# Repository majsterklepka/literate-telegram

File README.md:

# literate-telegram
moduł zasilacza stabilizowanego

Dwa moduły zasilacza stabilizowanego, przygotowane do wykonania jako DIY:

Moduły wykorzystują popularne liniowe stabilizatory napięcia stałego z rodziny 78xx i 79xx , kilka elementów dyskretnych, posiada bocznik prądowy.

Przygotowany został również projekt płytki drukowanej, oraz rysunek płytki w formacie PNG, 100x100mm, 2x2 moduły do wykonania w  domu. Rysunek płytki zawiera po 2 takie same moduły:

## Credits

Oczywiście jak i pozostałe moje projekty i ten jest udostępniany na zasadach Wolnych Licencji:

- [CC-BY-SA 4.0](https://creativecommons.org/licenses/by-sa/4.0/ "License")

Co mogę dodać? => Baw się dobrze, podziel się tym projektem z przyjaciółmi i niezapominaj o Autorze(ach);)

_MSc. Paweł Sobótka (SQ7EQE)_

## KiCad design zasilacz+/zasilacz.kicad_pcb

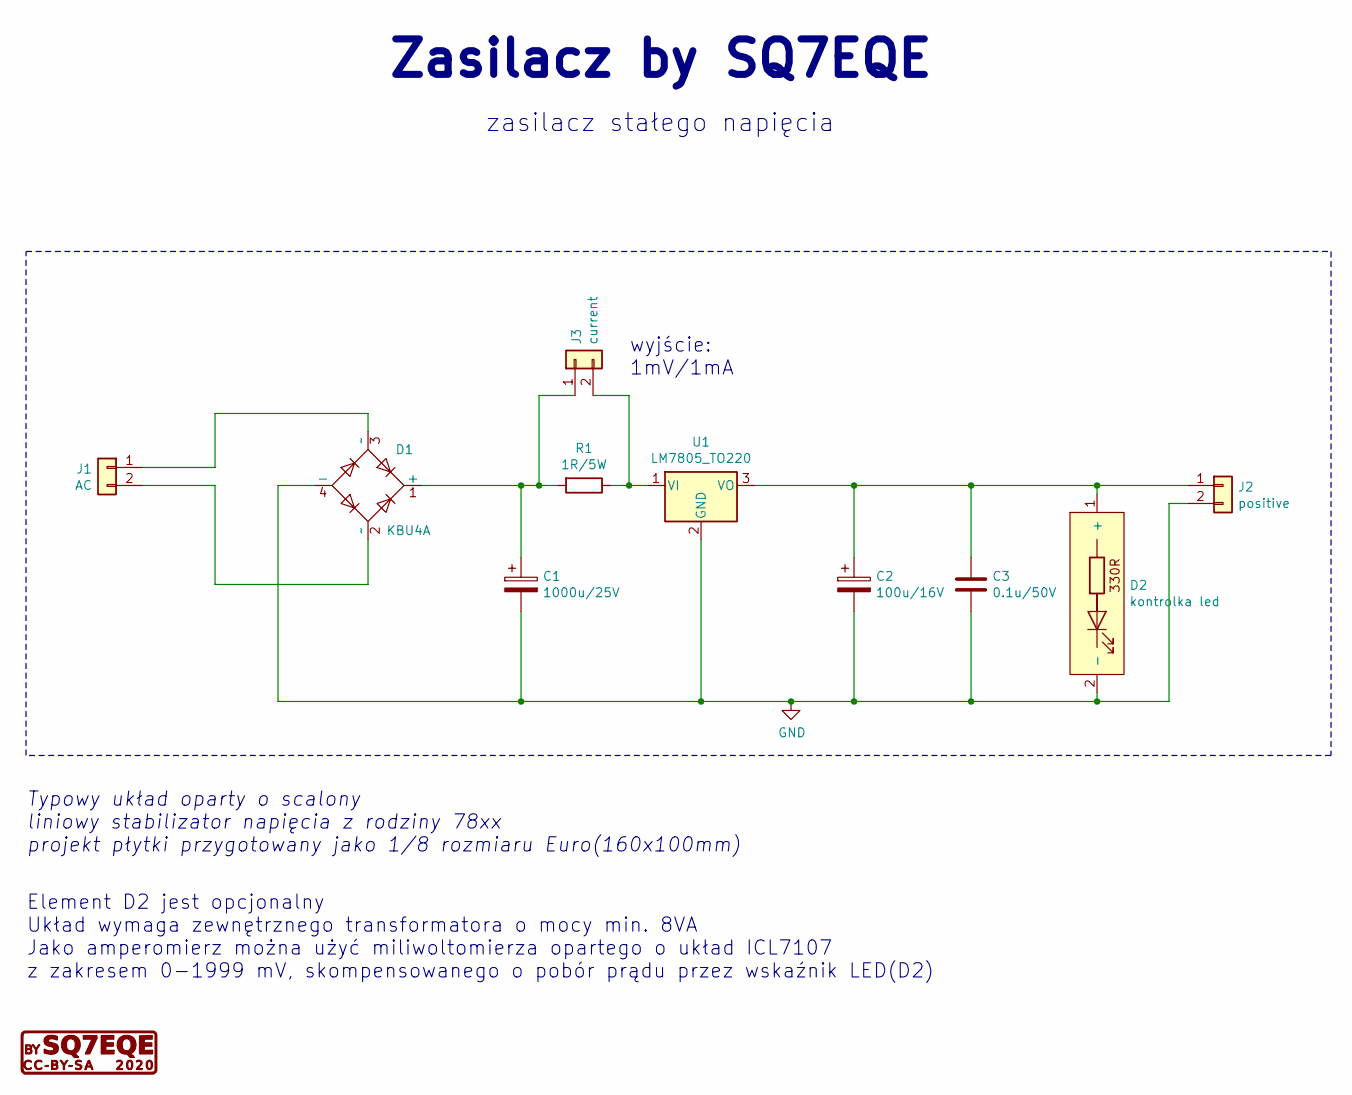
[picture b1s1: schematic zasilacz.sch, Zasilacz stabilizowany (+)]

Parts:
C1: 1000u/25V; CP_Radial_D10.0mm_P5.00mm
C2: 100u/16V; CP_Radial_D7.5mm_P2.50mm
C3: 0.1u/50V; C_Rect_L4.6mm_W5.5mm_P2.50mm_MKS02_FKP02
D1: KBU4A; Diode_Bridge_Vishay_KBU
D2: kontrolka led; led-indicators
J1: AC; conn-01x02_5.08mm
J2: positive; conn-01x02_5.08mm
J3: current; conn-01x02_5.08mm
R1: 1R/5W; R_Axial_Power_L25.0mm_W9.0mm_P27.94mm
U1: LM7805_TO220; TO-220-3_Vertical

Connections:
GND: C1.2, C2.2, C3.2, D1.4 (-), D2.2 (-), J2.2, U1.2 (GND)
unnamed: C1.1, D1.1 (+), J3.1, R1.2
unnamed: C2.1, C3.1, D2.1 (+), J2.1, U1.3 (VO)
unnamed: D1.2 (~~), J1.2
unnamed: D1.3 (~~), J1.1
unnamed: J3.2, R1.1, U1.1 (VI)

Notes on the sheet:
Typowy układ oparty o scalony liniowy stabilizator napięcia z rodziny 78xx projekt płytki przygotowany jako 1/8 rozmiaru Euro(160x100mm)
Element D2 jest opcjonalny Układ wymaga zewnętrznego transformatora o mocy min. 8VA Jako amperomierz można użyć miliwoltomierza opartego o układ ICL7107 z zakresem 0-1999 mV, skompensowanego o pobór prądu przez wskaźnik LED(D2)
wyjście: 1mV/1mA
Zasilacz by SQ7EQE
zasilacz stałego napięcia

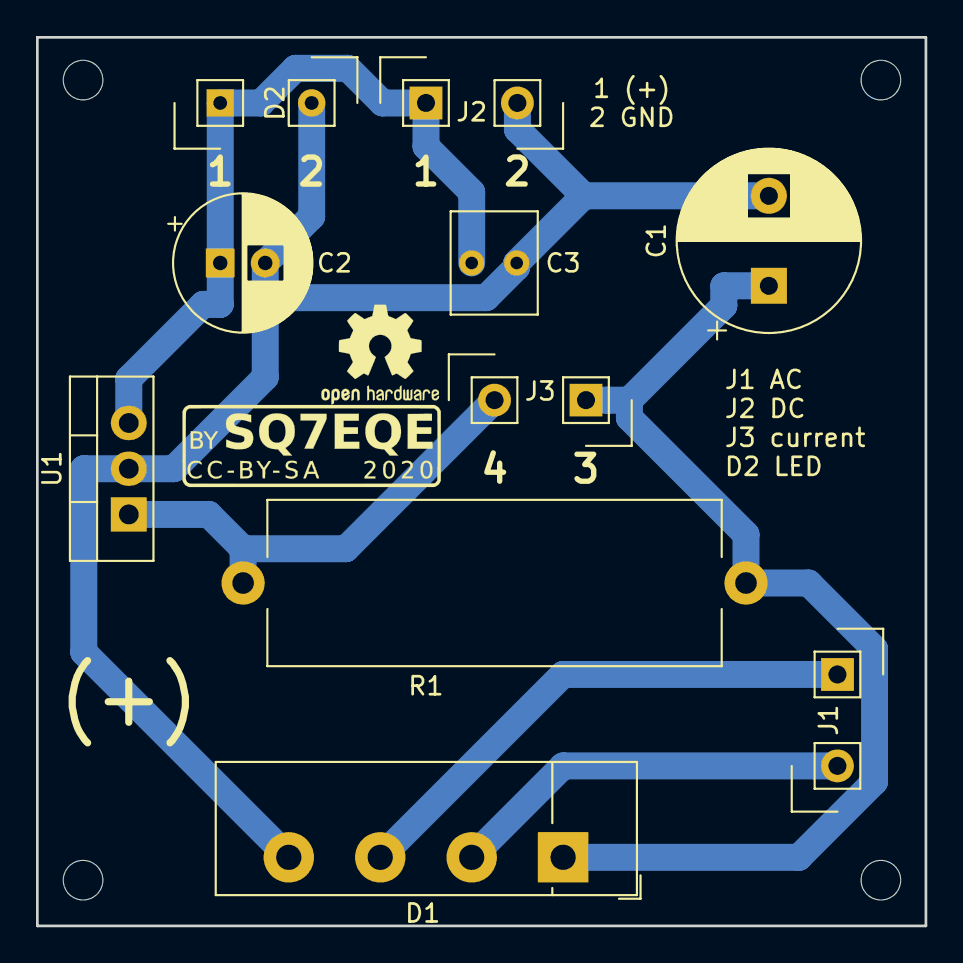
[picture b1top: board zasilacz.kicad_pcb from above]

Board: 2 copper layers, 49.4 x 49.4 mm, 14 parts (0 on the bottom side), 6 nets.

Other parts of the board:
M1, M2, M3, M4: MountingHole_2.2mm_M2

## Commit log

2020-04-07 update file
2020-04-07 new file
2020-04-07 Set theme jekyll-theme-minimal
2020-04-07 update file, change size & redesign
2020-08-17 cookies policy script included
2020-08-17 modified link to script
